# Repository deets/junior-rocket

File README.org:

* Junior Rocket Firmware

This repository contains the Arduino based firmware for the FAR Junior
two stage rocket.

** RP2040

The state machine is written in C++17. To allow for this to work with
Arduino, the =platform.txt= needs to change so that it enables C++17.

On my system, this is the file

 =~/Library/Arduino15/packages/arduino/hardware/mbed_rp2040/4.0.2/=

The following line must be present:

#+begin_src python
compiler.cpp.extra_flags=-std=gnu++17
#+end_src

Compile with

#+begin_src bash
arduino-cli compile --fqbn arduino:mbed_rp2040:pico
#+end_src

** Arduino Maple

Compile with

#+begin_src bash
arduino-cli compile --fqbn STMicroelectronics:stm32:GenF1 --board-options "pnum=MAPLEMINI_F103CB,opt=oslto"
#+end_src

*** Linker optimization in platform.txt

Lives in

#+begin_src bash
~/Library/Arduino15/packages/STMicroelectronics/hardware/stm32/2.5.0/
#+end_src

for me. Make the following settings look like this:

#+begin_src python
compiler.ldflags=-Wl,--no-warn-rwx-segments,--gc-sections
compiler.c.extra_flags=-ffunction-sections -fdata-sections
compiler.cpp.extra_flags=-ffunction-sections -fdata-sections
#+end_src

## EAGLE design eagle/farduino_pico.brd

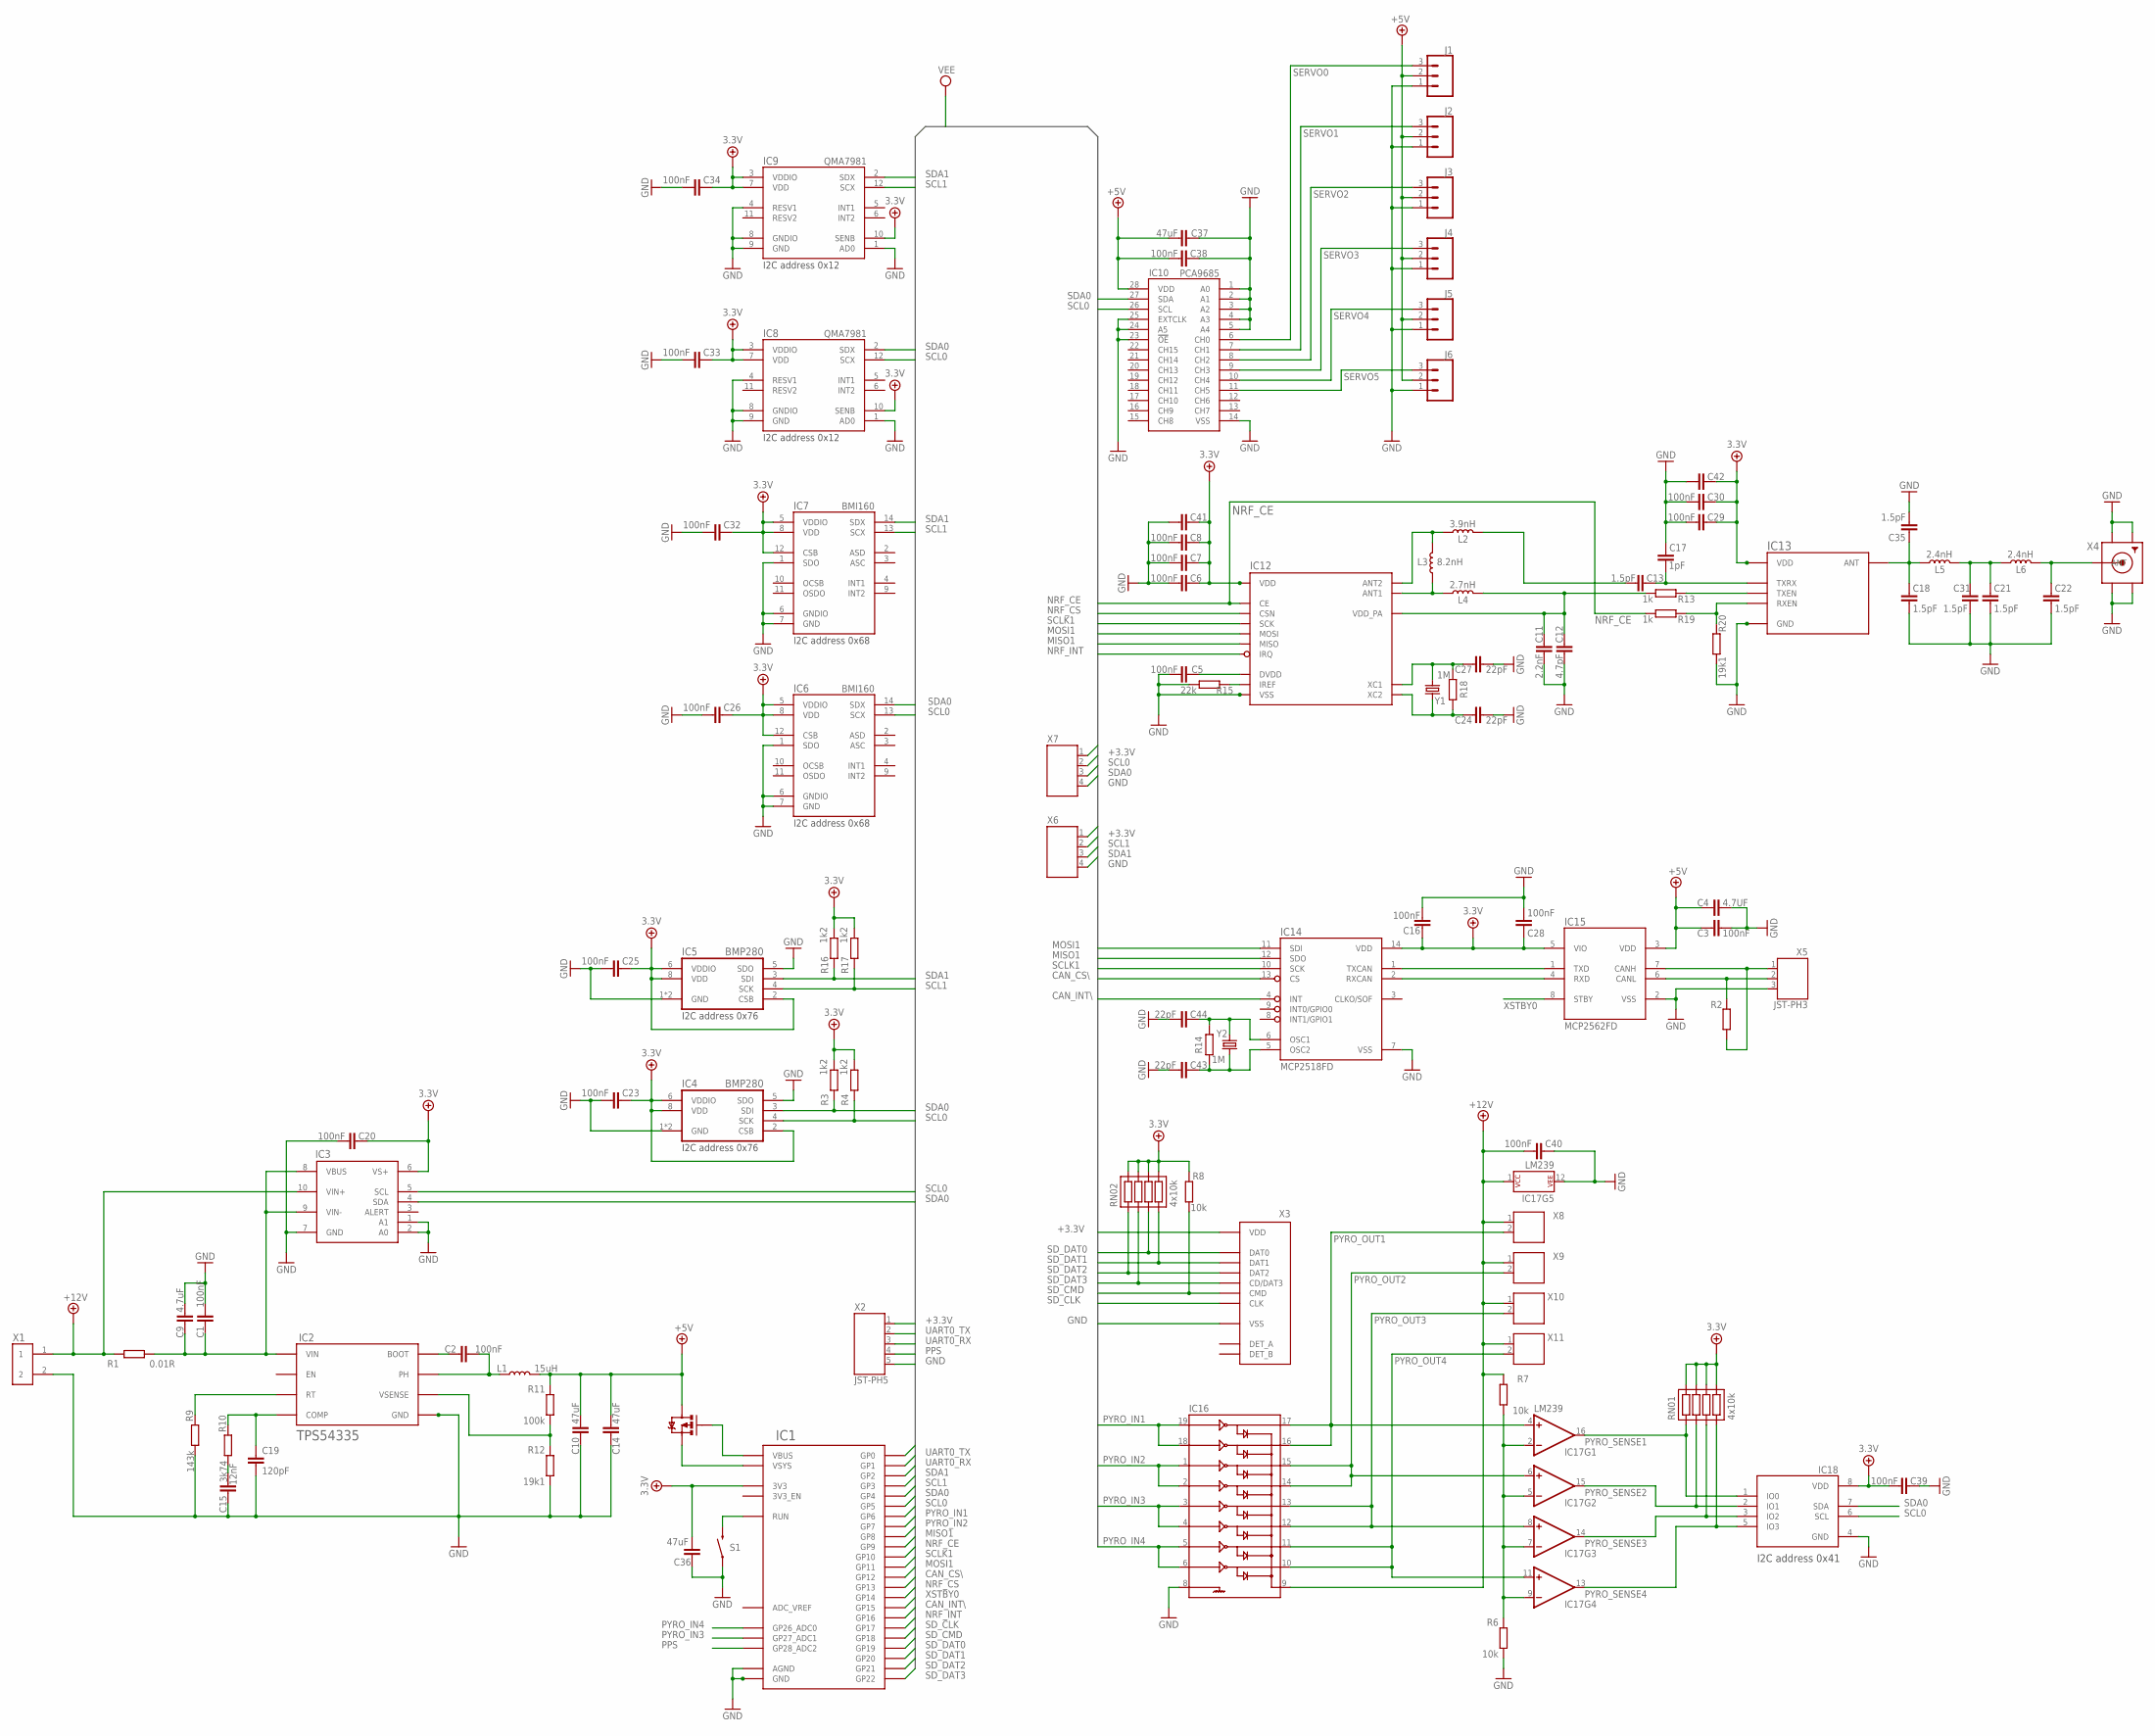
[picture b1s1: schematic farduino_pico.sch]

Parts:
C1, C2, C3, C5, C6, C7, C8, C16, C20, C23, C25, C26, C28, C29, C30, C32, C33, C34, C38, C39, C40: 100nF; 0402
C4, C41, C42: 4.7UF; 0402
C9: 4.7uF; 1206
C10, C14, C36, C37: 47uF; 1206
C11: 2.2nF; C0402
C12: 4.7pF; C0402
C13, C18, C21, C22, C31, C35: 1.5pF; C0402
C15: 12nF; C0402
C17: 1pF; C0402
C19: 120pF; C0402
C24, C27, C43, C44: 22pF; C0402
IC1: RPI_PICO-SMD; RPI_PICO
IC2: TPS54335ADRCR; VSON-10
IC3: INA226; VSSOP-10
IC4, IC5: BMP280
IC6, IC7: BMI160
IC8, IC9: QMA7981; LGA-12-2X2
IC10: PCA9685; TSSOP-28_4MM
IC12: NRF24L01SMD; QFN20-4X4MM
IC13: RFX2401C; QFN-16-3X3MM
IC14: MCP2518FD; SO14
IC15: MCP2562FD; SO08
IC16: ULN2803QFN; QFN-20-4X4
IC17: LM239; QFN16
IC18: PCA9536; HVSON8
J1, J2, J3, J4, J5, J6: CONN_03; 1X03
L1: 15uH; YSPIA0850
L2: 3.9nH; 0402
L3: 8.2nH; 0402
L4: 2.7nH; 0402
L5, L6: 2.4nH; 0402
Q1: DMG2305UX; SOT23-3@1
R1: 0.01R; R1206
R2: 120; R0402
R3, R4, R16, R17: 1k2; R0402
R6, R7, R8: 10k; R0402
R9: 143k; R0402
R10: 3k74; R0402
R11: 100k; R0402
R12, R20: 19k1; R0402
R13, R19: 1k; R0402
R14, R18: 1M; R0402
R15: 22k; R0402
RN01, RN02: 4x10k; 4D02
S1: MOMENTARY-SWITCH-SPST; TACTILE_SWITCH_SMD_4.2X3.2MM
X1: XT_CONN; XT30_PCB
X2: JST-PH5
X3: 5033981892
X4: SMACONNECTOR; SMA90_DIP
X5: JST-PH3
X6, X7: JST-PH4
X8, X9, X10, X11: JST-PH2
Y1, Y2: CRYSTAL-16MHZ; SMD3225

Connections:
+3.3V: C6.1, C7.1, C8.1, C16.1, C20.2, C23.1, C25.1, C26.1, C28.1, C29.1, C30.1, C32.1, C33.1, C34.1, C36.2, C39.2, C41.2, C42.2, IC1.3V3, IC3.6 (VS+), IC4.2 (CSB), IC4.6 (VDDIO), IC4.8 (VDD), IC5.2 (CSB), IC5.6 (VDDIO), IC5.8 (VDD), IC6.5 (VDDIO), IC6.8 (VDD), IC6.12 (CSB), IC7.5 (VDDIO), IC7.8 (VDD), IC7.12 (CSB), IC8.3 (VDDIO), IC8.7 (VDD), IC8.10 (SENB), IC9.3 (VDDIO), IC9.7 (VDD), IC9.10 (SENB), IC12.7 (VDD), IC12.15 (VDD), IC12.18 (VDD), IC13.14 (VDD), IC13.16 (VDD), IC14.14 (VDD), IC15.5 (VIO), IC18.8 (VDD), R3.2, R4.2, R8.2, R16.2, R17.2, RN01.5, RN01.6, RN01.7, RN01.8, RN02.5, RN02.6, RN02.7, RN02.8, X2.1, X3.4 (VDD), X6.1, X7.1
+5V: C3.1, C4.1, C10.2, C14.2, C37.2, C38.2, IC10.28 (VDD), IC15.3 (VDD), J1.2, J2.2, J3.2, J4.2, J5.2, J6.2, L1.2, Q1.3 (D), R11.2
+12V: C40.2, IC3.10 (VIN+), IC16.9 (COM), IC17.1 (P$V+), R1.2, R7.2, X1.1, X8.1, X9.1, X10.1, X11.1
ANT1: IC12.12 (ANT1), L3.1, L4.1
ANT2: IC12.13 (ANT2), L2.1, L3.2
CAN1_H: IC15.7 (CANH), R2.1, X5.1
CAN1_L: IC15.6 (CANL), R2.2, X5.2
CAN_CS\: IC1.GP12, IC14.13 (CS)
CAN_INT\: IC1.GP15, IC14.4 (INT)
DCDC_BOOT: C2.2, IC2.9 (BOOT)
DCDC_COMP: C19.1, IC2.7 (COMP), R10.1
DCDC_PH: C2.1, IC2.2 (PH), L1.1
DCDC_RT: IC2.10 (RT), R9.1
DVDD: C5.1, IC12.19 (DVDD)
FILTER1: C21.1, C31.1, L5.2, L6.1
GND: C1.1, C3.2, C4.2, C5.2, C6.2, C7.2, C8.2, C9.2, C10.1, C11.2, C12.2, C14.1, C15.2, C16.2, C17.1, C18.2, C19.2, C20.1, C21.2, C22.2, C23.2, C24.2, C25.2, C26.2, C27.2, C28.2, C29.2, C30.2, C31.2, C32.2, C33.2, C34.2, C35.2, C36.1, C37.1, C38.1, C39.1, C40.1, C41.1, C42.1, C43.2, C44.2, IC1.AGND, IC1.GND@1 (GND), IC1.GND@2 (GND), IC1.GND@3 (GND), IC1.GND@4 (GND), IC1.GND@5 (GND), IC1.GND@6 (GND), IC1.GND@7 (GND), IC1.GND@8 (GND), IC2.3 (GND), IC2.4 (GND), IC2.5 (GND), IC2.11 (GND), IC3.1 (A1), IC3.2 (A0), IC3.7 (GND), IC4.1 (GND), IC4.5 (SDO), IC4.7 (GND), IC5.1 (GND), IC5.5 (SDO), IC5.7 (GND), IC6.1 (SDO), IC6.6 (GNDIO), IC6.7 (GND), IC7.1 (SDO), IC7.6 (GNDIO), IC7.7 (GND), IC8.1 (AD0), IC8.4 (RESV1), IC8.8 (GNDIO), IC8.9 (GND), IC9.1 (AD0), IC9.4 (RESV1), IC9.8 (GNDIO), IC9.9 (GND), IC10.1 (A0), IC10.2 (A1), IC10.3 (A2), IC10.4 (A3), IC10.5 (A4), IC10.14 (VSS), IC10.23 (!OE), IC10.24 (A5), IC10.25 (EXTCLK), IC12.0 (VSS), IC12.8 (VSS), IC12.14 (VSS), IC12.17 (VSS), IC12.20 (VSS), IC13.1 (GND), IC13.2 (GND), IC13.3 (GND), IC13.7 (GND), IC13.8 (GND), IC13.9 (GND), IC13.11 (GND), IC13.12 (GND), IC13.15 (GND), IC13.17 (GND), IC14.7 (VSS), IC15.2 (VSS), IC16.8 (GND), IC17.12 (P$V-), IC18.4 (GND), J1.1, J2.1, J3.1, J4.1, J5.1, J6.1, R6.1, R9.2, R12.1, R15.1, R20.1, S1.1, S1.2 (1), X1.2, X2.5, X3.6 (VSS), X4.GND1, X4.GND2, X4.GND3, X4.GND4, X5.3, X6.4, X7.4
IREF: IC12.16 (IREF), R15.2
MISO1: IC1.GP8, IC12.5 (MISO), IC14.12 (SDO)
MOSI1: IC1.GP11, IC12.4 (MOSI), IC14.11 (SDI)
unnamed: C15.1, R10.2
NRF_CE: IC1.GP9, IC12.1 (CE), R19.1
NRF_CS: IC1.GP13, IC12.2 (CSN)
NRF_INT: IC1.GP16, IC12.6 (IRQ)
NRF_SIGNAL: C13.2, L2.2
OSC1_40MHZ: C44.1, IC14.6 (OSC1), R14.2, Y2.3 (2)
OSC2_40MHZ: C43.1, IC14.5 (OSC2), R14.1, Y2.1
PA_ANT: C18.1, C35.1, IC13.10 (ANT), L5.1
PPS: IC1.GP28_A2 (GP28_ADC2), X2.4
PYRO_IN1: IC1.GP6, IC16.18 (IN2), IC16.19 (IN1)
PYRO_IN2: IC1.GP7, IC16.1 (IN3), IC16.2 (IN4)
PYRO_IN3: IC1.GP27_A1 (GP27_ADC1), IC16.3 (IN5), IC16.4 (IN6)
PYRO_IN4: IC1.GP26_A0 (GP26_ADC0), IC16.5 (IN7), IC16.6 (IN8)
PYRO_OUT1: IC16.16 (OUT2), IC16.17 (OUT1), IC17.4 (+IN), X8.2
PYRO_OUT2: IC16.14 (OUT4), IC16.15 (OUT3), IC17.6 (+IN), X9.2
PYRO_OUT3: IC16.12 (OUT6), IC16.13 (OUT5), IC17.8 (+IN), X10.2
PYRO_OUT4: IC16.10 (OUT8), IC16.11 (OUT7), IC17.11 (+IN), X11.2
PYRO_SENSE1: IC17.16 (OUT), IC18.1 (IO0), RN01.1
PYRO_SENSE2: IC17.15 (OUT), IC18.2 (IO1), RN01.2
PYRO_SENSE3: IC17.14 (OUT), IC18.3 (IO2), RN01.3
PYRO_SENSE4: IC17.13 (OUT), IC18.5 (IO3), RN01.4
RUN: IC1.RUN, S1.3 (2), S1.4 (2)
RXCAN1: IC14.2 (RXCAN), IC15.4 (RXD)
RXEN: IC13.6 (RXEN), R19.2, R20.2
SCL0: IC1.GP5, IC3.5 (SCL), IC4.4 (SCK), IC6.13 (SCX), IC8.12 (SCX), IC10.26 (SCL), IC18.6 (SCL), R4.1, X7.2
SCL1: IC1.GP3, IC5.4 (SCK), IC7.13 (SCX), IC9.12 (SCX), R17.1, X6.2
SCLK1: IC1.GP10, IC12.3 (SCK), IC14.10 (SCK)
SDA0: IC1.GP4, IC3.4 (SDA), IC4.3 (SDI), IC6.14 (SDX), IC8.2 (SDX), IC10.27 (SDA), IC18.7 (SDA), R3.1, X7.3
SDA1: IC1.GP2, IC5.3 (SDI), IC7.14 (SDX), IC9.2 (SDX), R16.1, X6.3
SD_CLK: IC1.GP17, X3.5 (CLK)
SD_CMD: IC1.GP18, R8.1, X3.3 (CMD)
SD_DAT0: IC1.GP19, RN02.3, X3.7 (DAT0)
SD_DAT1: IC1.GP20, RN02.4, X3.8 (DAT1)
SD_DAT2: IC1.GP21, RN02.1, X3.1 (DAT2)
SD_DAT3: IC1.GP22, RN02.2, X3.2 (CD/DAT3)
SERVO0: IC10.6 (CH0), J1.3
SERVO1: IC10.7 (CH1), J2.3
SERVO2: IC10.8 (CH2), J3.3
SERVO3: IC10.9 (CH3), J4.3
SERVO4: IC10.10 (CH4), J5.3
SERVO5: IC10.11 (CH5), J6.3
SMA_RF: C22.1, L6.2, X4.ANTENNA (ANT)
TXCAN1: IC14.1 (TXCAN), IC15.1 (TXD)
TXEN: IC13.5 (TXEN), R13.2
TXRX: C13.1, C17.2, IC13.4 (TXRX)
UART0_RX: IC1.GP1, X2.3
UART0_TX: IC1.GP0, X2.2
UREF: IC17.2 (-IN), IC17.5 (-IN), IC17.7 (-IN), IC17.9 (-IN), R6.2, R7.1
VBUS: IC1.VBUS, Q1.1 (G)
VDD_PA: C11.1, C12.1, IC12.11 (VDD_PA), L4.2, R13.1
VIN: C1.2, C9.1, IC2.1 (VIN), IC3.8 (VBUS), IC3.9 (VIN-), R1.1
VSENSE: IC2.6 (VSENSE), R11.1, R12.2
VSYS: IC1.VSYS, Q1.2 (S)
XC1_16MHZ: C27.1, IC12.10 (XC1), R18.1, Y1.1
XC2_16MHZ: C24.1, IC12.9 (XC2), R18.2, Y1.3 (2)
XSTBY0: IC1.GP14, IC15.8 (STBY)

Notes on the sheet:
I2C address 0x41
I2C address 0x76
I2C address 0x68
I2C address 0x12

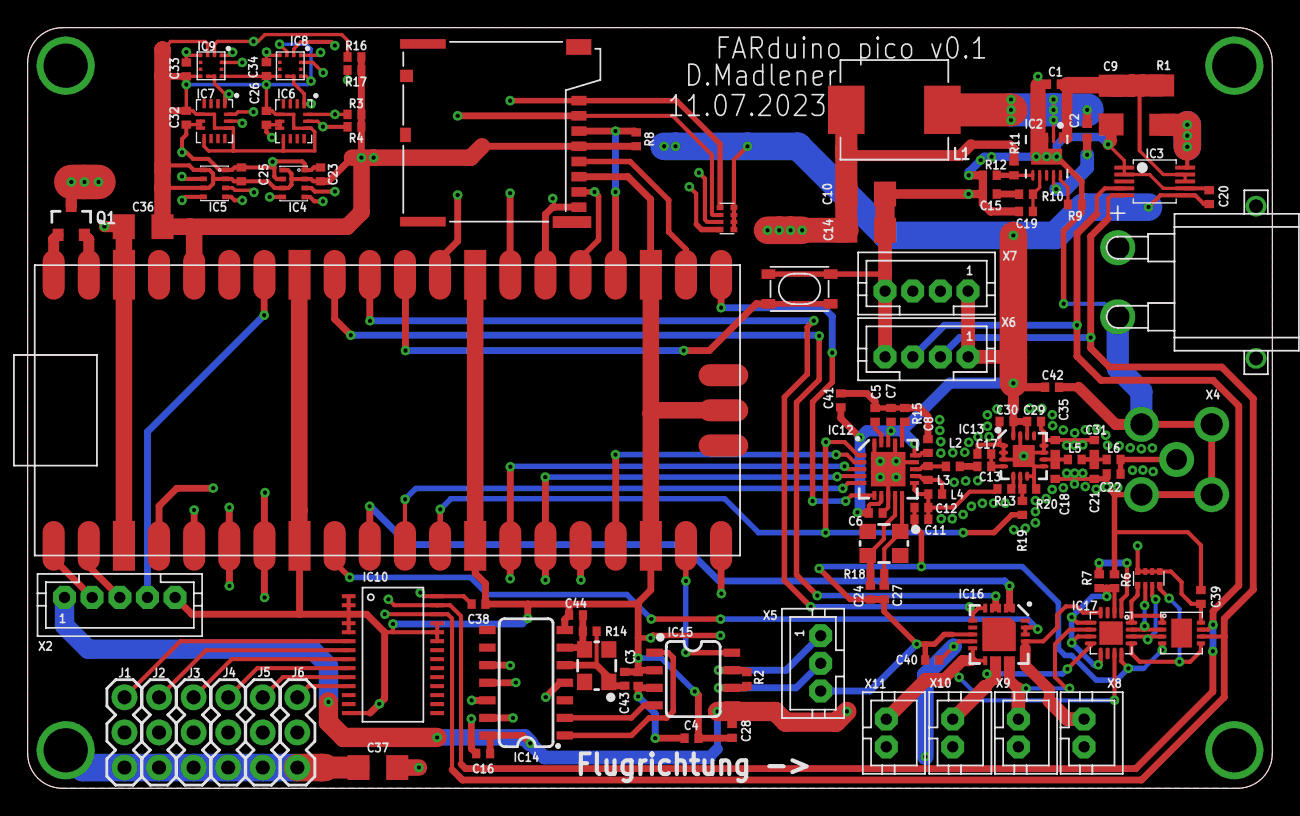
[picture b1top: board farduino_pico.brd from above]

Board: 4 copper layers, 90.0 x 55.0 mm, 109 parts (0 on the bottom side), 75 nets.

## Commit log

2023-06-09 Pull in upstream repo code
    This is awkward, but due to the limitations of the Arduino platform
    I don't see a better way - submodules aren't really working here.
2023-06-09 Replace current state logic with state machine and observer
2023-06-09 Pulled in latest code from upstream
    This avoids a preprocessor name conflict and removes iostream usage
2023-06-09 Refactor: clarify timestamp arithmetic
2023-06-09 Cleanup and mock-compile on RP2040
2023-06-09 Documentation update
2023-06-09 Re-organize includes and remove test preprocessor statement
2023-06-09 Add .gitattributes
2023-06-09 Use std::chrono
2023-08-08 FARduino pico schematic and board file

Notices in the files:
parts and their libraries:
SparkFun-DiscreteSemi: Licensing: Creative Commons ShareAlike 4.0 International - https://creativecommons.org/licenses/by-sa/4.0
FaBo-Sensor: Released under the Creative Commons Attribution-ShareAlike 4.0 License
https://creativecommons.org/licenses/by-sa/4.0
